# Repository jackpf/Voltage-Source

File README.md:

# Voltage-Source (WIP)

Simple quad output static voltage generator.

Useful for for creating offsets, or modulating parameters that don't have dedicated knobs.

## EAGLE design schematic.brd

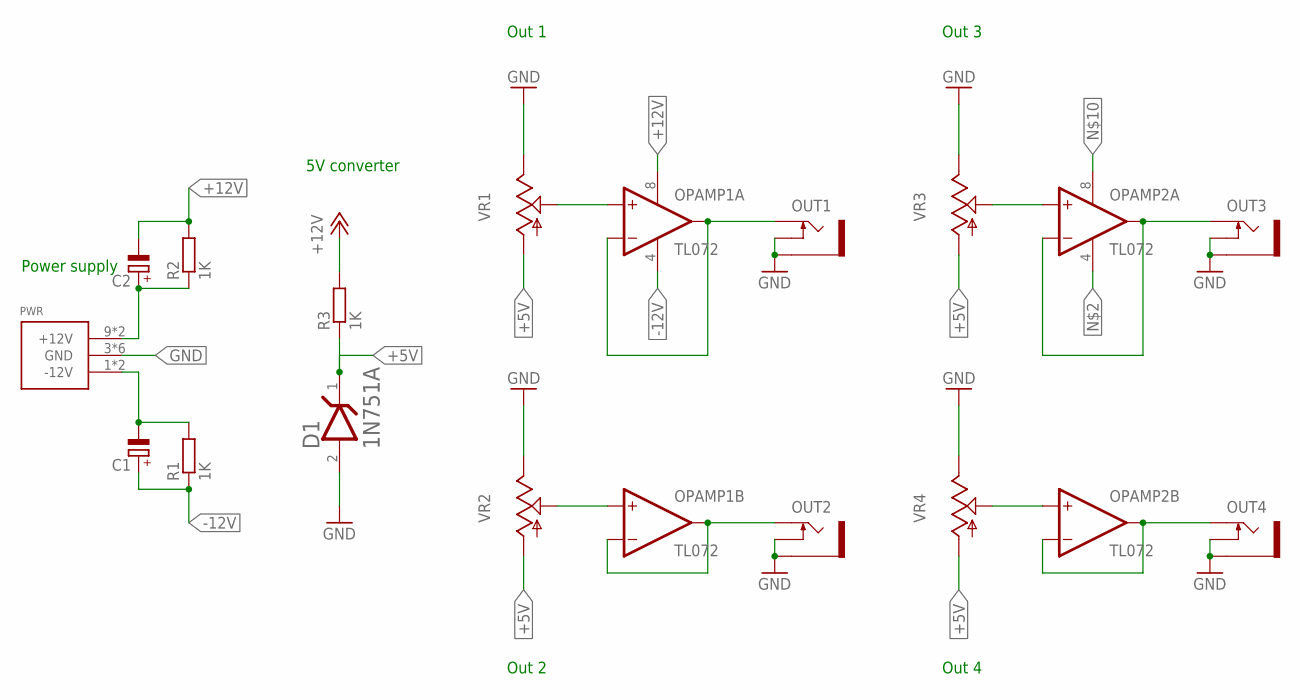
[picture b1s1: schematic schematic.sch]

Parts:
C1, C2: CPOL-EUE2.5-5V; E2,5-4R
D1: ON_SEMI_1N751AON_SEMI_1N751A_0_0; ON_SEMI_1N751A_0
OPAMP1, OPAMP2: TL072; DIL08-SML
OUT1, OUT2, OUT3, OUT4: THONKICONNNEW; WQP-PJ301M-12_JACK
PWR: POWER_SIMPLE10; POWER_10
R1, R2, R3: 1K; 0204/5; MPN CCF551K00FKE36
VR1, VR2, VR3, VR4: 9MM_SNAP-IN_POT_; 9MM_SNAP-IN_POT

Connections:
+5V: D1.1 (CATHODE), R3.1, VR1.1 (A), VR2.1 (A), VR3.1 (A), VR4.1 (A)
+12V: C2.+, OPAMP1.8 (V+), PWR.9 (+12V), PWR.10 (+12V), R2.1, R3.2
-12V: C1.-, OPAMP1.4 (V-), PWR.1 (-12V), PWR.2 (-12V), R1.2
GND: D1.2 (ANODE), OUT1.P$2_SWITCH (SWITCH), OUT1.P$3_SLEEVE (SLEEVE), OUT2.P$2_SWITCH (SWITCH), OUT2.P$3_SLEEVE (SLEEVE), OUT3.P$2_SWITCH (SWITCH), OUT3.P$3_SLEEVE (SLEEVE), OUT4.P$2_SWITCH (SWITCH), OUT4.P$3_SLEEVE (SLEEVE), PWR.3 (GND), PWR.4 (GND), PWR.5 (GND), PWR.6 (GND), PWR.7 (GND), PWR.8 (GND), VR1.3 (E), VR2.3 (E), VR3.3 (E), VR4.3 (E)
unnamed: OPAMP1.3 (+IN), VR1.2 (S)
unnamed: OPAMP1.6 (-IN), OPAMP1.7 (OUT), OUT2.P$1_TIP (TIP)
unnamed: OPAMP1.5 (+IN), VR2.2 (S)
unnamed: OPAMP2.1 (OUT), OPAMP2.2 (-IN), OUT3.P$1_TIP (TIP)
unnamed: OPAMP2.3 (+IN), VR3.2 (S)
unnamed: OPAMP2.6 (-IN), OPAMP2.7 (OUT), OUT4.P$1_TIP (TIP)
unnamed: OPAMP2.5 (+IN), VR4.2 (S)
unnamed: OPAMP1.1 (OUT), OPAMP1.2 (-IN), OUT1.P$1_TIP (TIP)
unnamed: C1.+, R1.1
unnamed: C2.-, R2.2

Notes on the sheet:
Power supply
5V converter
Out 1
Out 2
Out 3
Out 4

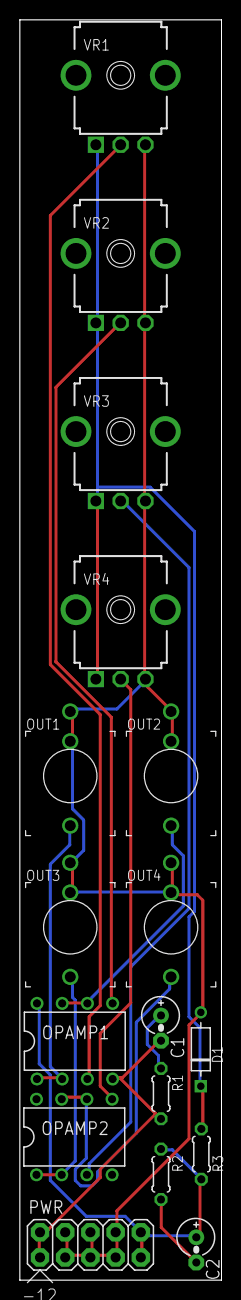
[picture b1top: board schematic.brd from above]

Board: 2 copper layers, 20.3 x 127.0 mm, 17 parts (0 on the bottom side), 14 nets.

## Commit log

2020-10-19 Ignore files
